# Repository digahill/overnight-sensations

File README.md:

# overnight-sensations

For build log posts, see the [build-posts folder](build-posts/).

You can find pics of the build process in the [build-pics folder](build-pics).

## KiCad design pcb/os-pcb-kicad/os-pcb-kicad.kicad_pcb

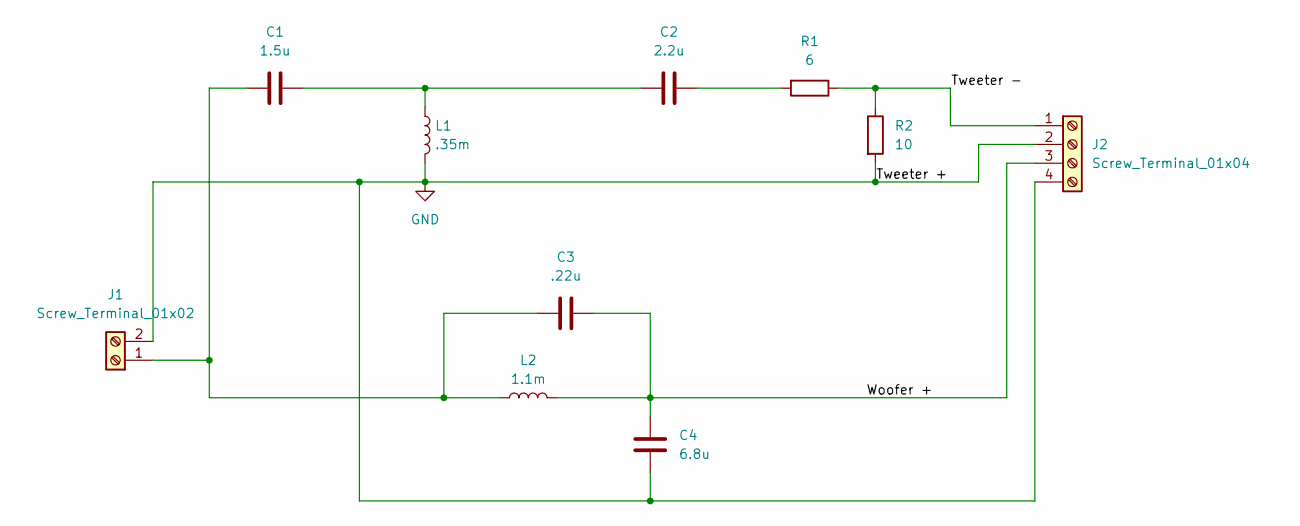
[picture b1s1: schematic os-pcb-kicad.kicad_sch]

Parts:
C1: 1.5u; CP_Axial_L30.0mm_D10.0mm_P35.00mm_Horizontal
C2: 2.2u; CP_Axial_L30.0mm_D15.0mm_P35.00mm_Horizontal
C3: .22u; CP_Axial_L18.0mm_D8.0mm_P25.00mm_Horizontal
C4: 6.8u; CP_Axial_L46.0mm_D20.0mm_P52.00mm_Horizontal
J1: Screw_Terminal_01x02; TerminalBlock_MaiXu_MX126-5.0-02P_1x02_P5.00mm
J2: Screw_Terminal_01x04; TerminalBlock_MaiXu_MX126-5.0-04P_1x04_P5.00mm
L1: .35m; L_Toroid_Vertical_L31.8mm_W15.9mm_P13.50mm_Bourns_5700
L2: 1.1m; L_Toroid_Horizontal_D41.9mm_P37.60mm_Vishay_TJ7
R1: 6; R_Axial_Shunt_L47.6mm_W12.7mm_PS34.93mm_P50.80mm
R2: 10; R_Axial_Shunt_L47.6mm_W12.7mm_PS34.93mm_P50.80mm

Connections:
/Tweeter -: J2.1, R1.1, R2.1
/Woofer +: C3.2, C4.2, J2.3, L2.2
GND: C4.1, J1.2, J2.2, J2.4, L1.2, R2.2
unnamed: C1.2, C2.1, L1.1
unnamed: C2.2, R1.2
unnamed: C1.1, C3.1, J1.1, L2.1

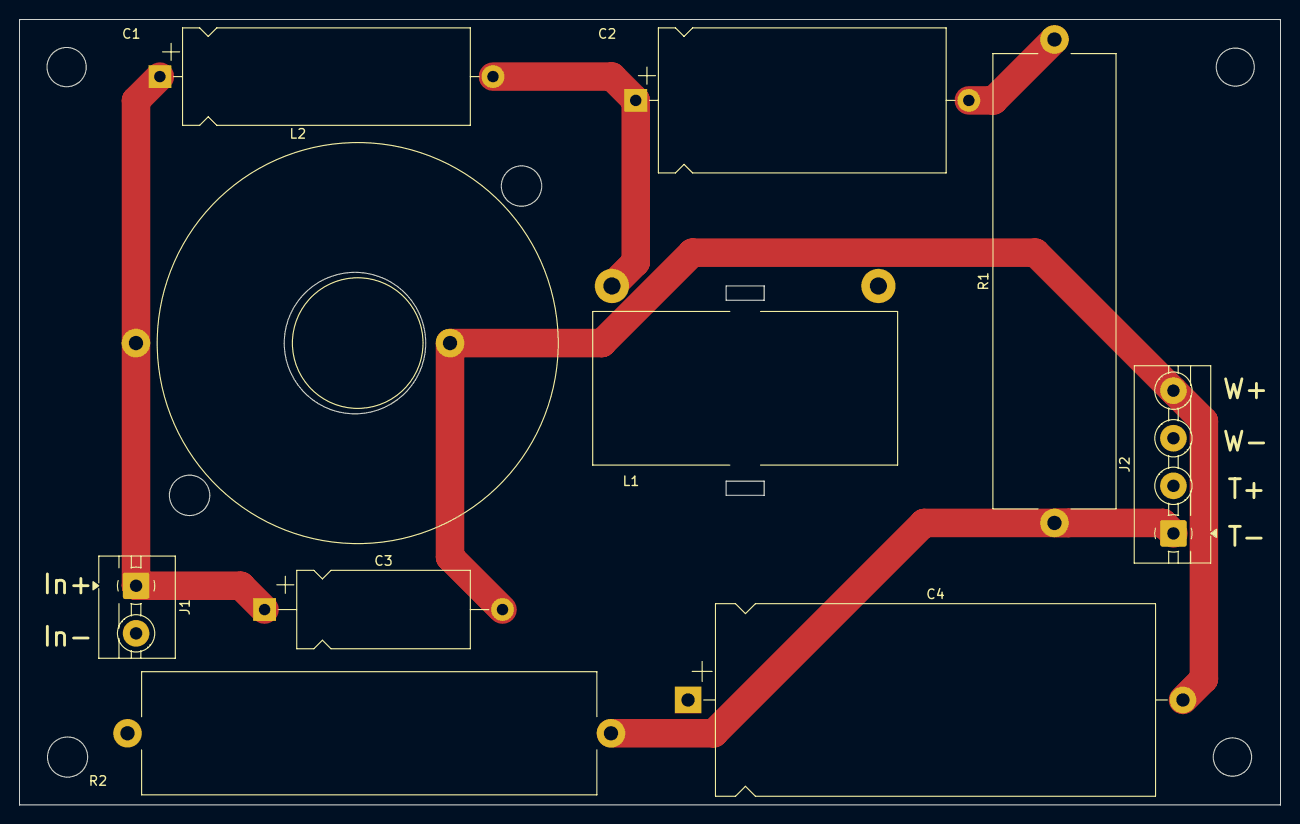
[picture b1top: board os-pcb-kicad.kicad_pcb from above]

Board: 2 copper layers, 132.5 x 82.5 mm, 10 parts (0 on the bottom side), 6 nets.

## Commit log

2025-01-31 initialized project
2025-02-03 Added REW directory.
2025-02-03 Added new build-pics
2025-02-03 Added first post as test.
2025-02-03 Renamed 3d-render files
2025-02-03 Added more posts.
2025-02-05 added new build post
2025-02-12 Adding glue up pics
2025-02-14 Added final pics
2025-02-15 new posts
2025-02-17 Updates to posts
